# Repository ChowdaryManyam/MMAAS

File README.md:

# Multi-Modular-Adaptor-for-Arduino-Shields-MMAAS
Multi Modular Adaptor for Arduino Shields

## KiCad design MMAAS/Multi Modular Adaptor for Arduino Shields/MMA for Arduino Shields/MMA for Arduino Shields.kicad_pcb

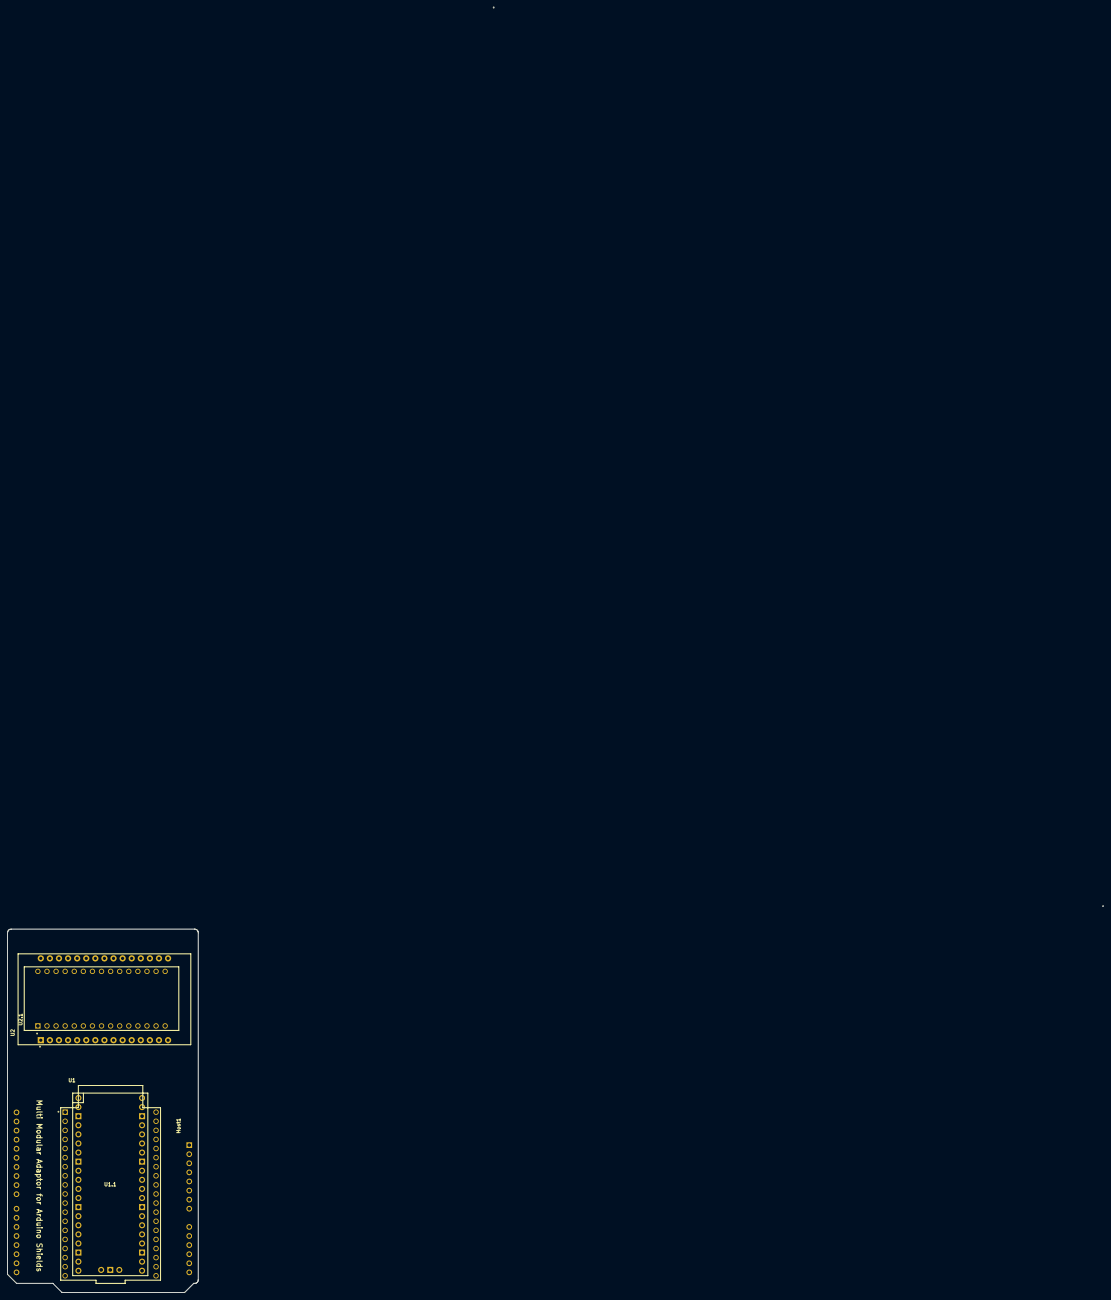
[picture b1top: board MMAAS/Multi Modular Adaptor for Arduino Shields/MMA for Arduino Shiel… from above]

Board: 2 copper layers, 53.3 x 101.5 mm, 5 parts (0 on the bottom side), 2 nets, no tracks yet.

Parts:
Host1: Arduino_Uno_Shield; UNO_R3_Arduino
U1: ESP32-DEVKITC
U1.1: Pi Pico; RPi_Pico_SMD_TH
U2: ESP8266; ESP8266-nodeMCU
U2.1: Nano; Nano_Arduino

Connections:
3v3: U1.1.36 (3V3_OUT), U2.11 (3V3), U2.16 (3V3), U2.25 (3V3), U2.1.17 (3V3)
unnamed: U2.10 (GND), U2.14 (GND), U2.17 (GND), U2.24 (GND)

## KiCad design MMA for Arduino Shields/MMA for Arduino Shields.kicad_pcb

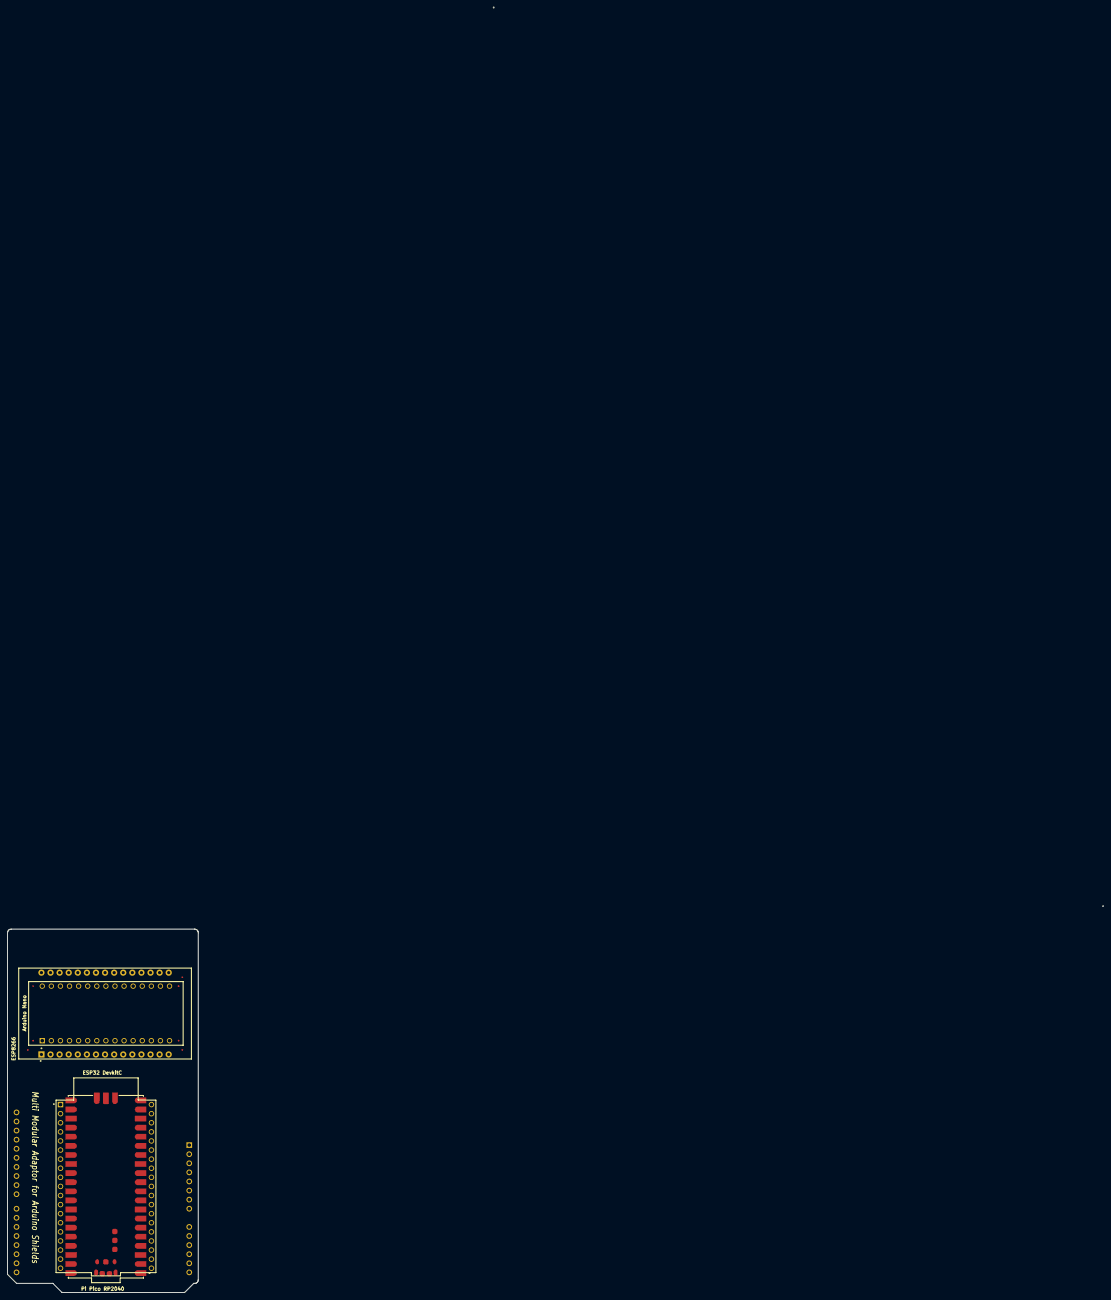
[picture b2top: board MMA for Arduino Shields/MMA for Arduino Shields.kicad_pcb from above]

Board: 2 copper layers, 53.3 x 101.5 mm, 5 parts (0 on the bottom side), 2 nets, no tracks yet.

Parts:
Arduino Nano: A000005; MODULE_A000005
ESP32 DevkitC: ESP32-DEVKITC; MODULE_ESP32-DEVKITC
ESP8266: ZC563900; MODULE_ZC563900
Multi Modular Adaptor for Arduino Shields: uno-arduino-r3
Pi Pico RP2040: SC0915; MODULE_SC0915

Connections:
unnamed: ESP8266.10 (GND), ESP8266.14 (GND), ESP8266.17 (GND), ESP8266.24 (GND)
unnamed: ESP8266.11 (3V3), ESP8266.16 (3V3), ESP8266.25 (3V3)
